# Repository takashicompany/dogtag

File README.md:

# DogTag

DogTagは9キーのコンパクトなマクロパッドです。  
100mm x 100mm 以内のPCBから組み立てます。  
リバーシブルに対応しており、2台をTRRSケーブルで接続することで分割型のマクロパッドとしても使用できます。  
その他にもロータリーエンコーダの搭載やMXソケットによるキースイッチの付け替え(ホットスワップ)も可能です。  
LEDによるアンダーグロウも可能です。  

DogTag is a compact macro pad with 9 keys.  
It is assembled from a PCB no larger than 100mm x 100mm.  
It is reversible and can be used as a split macro pad by connecting two units with a TRRS cable.  
Other features include a rotary encoder and MX sockets for hot-swapping of keyswitches.  
LED underglow is also available.  

## 必要な部品

### キットに同梱されているもの
|部品|個数|備考|
|:--|:--|:--|
|PCB|1|リードタイプと表面実装のダイオードに対応。|
|ダイオード（リードタイプ)|9||
|m2スペーサー(3.5mm)|5||
|m2ネジ(3mm)|10||
|リセットスイッチ|1||
|TRRSソケット|1||
|滑り止めシール|4||

### 別途用意するもの
|部品|個数|備考|
|:--|:--|:--|
|キースイッチ|9|Cherry MX互換のもの。|
|キーキャップ|9|全て1u。Chery MX互換のもの。|
|Pro Micro|1||
|USBケーブル|1|Pro MicroとPCを接続します。|

### オプション
|部品|個数|備考|
|:--|:--|:--|
|コンスルー|2|Pro Microに取り付けます。|
|MXソケット|9|キースイッチの付け替えが可能になります。|
|ロータリーエンコーダ|1|親指に近いキーにロータリーエンコーダを取り付けることができます。
|LED(SK6812MINI-E)|4|キーボードが光ります。|

## 組み立て方

以下の組み立て方は左手用になります。
右手側の場合は基板を裏返して組み立ててください。

### 1. トッププレートとPCBを切り離す

トッププレートとPCBが結合しているので、これを切り離します。  
(場合によっては切り離し済みのケースがあります。)  

基板を接続部の折れ線に沿って曲げると切り離せます。  

残った接続部分はペンチなどで折ると取りやすいです。  
折った場所をヤスリがけすると仕上がりがキレイになります。  

### 2. ダイオードをはんだ付けする  

ダイオードを取り付けます。  
余談ですが、ダイオードは電流の向きを制御する役割があります。  
自作キーボードでは主にキーが同時に押されたことを検知する役割があります。  
以上のことは知らなくても当キーボードは完成させられますのでご安心ください🙏  

ダイオードが基板のはんだ付け穴に入るように足を曲げます。  

ダイオードをはんだ付け穴に挿します。  
ダイオードの端の黒い線が、基板の矢印(|◁)側になるようにPCBに挿します。

はんだ付けをするために基板を反対側にします。  
この時、ダイオードの足を少し開くとPCBから抜けづらくなります。  

はんだ付けを行います。  
はんだ付けがはじめての方は[こちら](https://www.youtube.com/watch?v=iCJXT3d4140)の動画を参考に進めるとスムーズに行くかと思います。  
(難しそうなイメージがありますが、要はくっついていれば良いのです)

はんだ付けが済んだら、ニッパーで足を切ります。  

合計9箇所をはんだ付けします。  
**ダイオードの向きが写真と異なっていないかを確認してください。**

### 3. リセットスイッチの取り付け

リセットスイッチはファームウェアを書き込む際などに使用します。  

取り付け位置はキーボードの手前の「RESET」の印刷がされている箇所です。  

穴にリセットスイッチの足を挿し込みます。  

基板をひっくり返してリセットスイッチの足が穴から出ていることを確認します。   

はんだ付けを行います。  

はんだ付けを済ませたらニッパーなどではんだ付け部分を切り取り、可能な限り平らにするとキーボードが安定しやすくなります。  

### 4. TRRSソケットの取り付け

TRRSソケットは、分割キーボードとして利用する場合にキーボード同士を繋げるために使います。  
単体で使う場合は使用しませんが、気が変わって両手分欲しくなっても良いように取り付けましょう笑  

取り付け位置は、基板手前側の「TRRS」と印刷されている箇所です。

穴に沿って挿し込みます。  
いくつか穴が余ってしまうのは、右手側で利用する際の穴です。  

はんだ付けの際にひっくり返す時にTRRSソケットが抜けてしまう場合は、マスキングテープなどで固定すると良いです。  

ひっくり返して、リセットスイッチと同様にはんだ付けを行います。  

### 4.5 LEDの取り付け

(LEDを取り付けない方は、この項目はスキップして問題ありません。)

Rev2以降の基板ではSK6812MINI-Eを取り付け、DogTagを光らせることができます。

下の写真と同じく、PCBの底面に取り付けることで表側へLEDの光が届くようになります。  

### 5. トッププレートの取り付け  

トッププレートを取り付けます。  
**取り付けるPro Microによっては、トッププレートと干渉してしまう場合があるので、必要に応じてヤスリなどで削るとスムーズに取り付けられるかと思います。**  

ネジが2種類同梱されている場合は、左の頭が小さいネジはトッププレート側(表側)、右の頭が大きいネジはボトムプレート側(底面側)に使用します。  

取り付けにはネジとスペーサーを使用します。  

赤丸の位置に、スペーサーをネジで固定します。  

このように5箇所にスペーサーを取り付けます。  

最後にトッププレートを取り付けます。  
スペーサーとトッププレートをネジで固定します。  

### 6. Pro Microの取り付け。

Pro Microはキーボードの頭脳となる部分です。  
キースイッチが押されたことを検知して、PCにキーの入力を伝えます。  
Pro MicroをPCBに固定する際は[コンスル](https://shop.yushakobo.jp/products/31)ーという部品を用いるのがオススメです。  
コンスルーを使うと、Pro Microを基板から楽に取り外せるので、メンテナンスがしやすかったり、他の自作キーボードに使い回すことが容易になります。  

[コンスルーがはんだ付けされたものが遊舎工房さんで販売されている](https://shop.yushakobo.jp/products/a0500ph?variant=37665498497185)ので、難しそう…と感じた方は購入するのもアリだと思います。

Pro Microにコンスルーを挿します。  
左手側の場合はPro Microのチップなどが配置されている側が裏になるようにしてください。  
(右手側の場合は逆にチップ側が表になるようにしてください。)  

コンスルーでPro MicroとPCBを接続します。  

Pro Microをはんだ付けします。  
トッププレートとPro Microがぶつかってしまうことがあるので、正しく挿されているか側面から確認するとミスを避けられます。 

全ての端子をはんだ付けできたら完了です。  

### 7. キースイッチのはんだ付け

キースイッチを取り付けます。  

キースイッチの取り付け方は2種類あります。

#### a. キースイッチを直にはんだ付けする場合

キースイッチをトッププレートに挿し込みます。  

キースイッチの足がはんだ付け穴(周りが銀箔になっている)から出ていることを確認します。　　

キースイッチの足をはんだ付けします。  

#### b. MXソケットを使う場合  

MXソケットをPCBにはんだ付けし、キースイッチをMXソケットで固定する方式です。  
手間が増えますが、キースイッチを付け替えられることがメリットです。  

MXソケットのプリントのうち片方のはんだ付け箇所に事前にはんだを載せておきます。(予備ハンダというそうです。)  

MXソケットをピンセットで抑えながら、予備ハンダを溶かしながらMXソケットの片方をはんだ付けします。  

もう一方のはんだ付け箇所もはんだ付けして完了です。  
表面からキースイッチをMXソケットに挿し込みます。  

9箇所にキースイッチを挿し込めば完了です。  

### 8. ゴム足を付ける

ゴム足をつけて完成です。  

底面に取り付けます。  

### 9. キーキャップを取り付ける

最後にキーキャップを取り付けて完成です。  

### 10. ファームウェアの書き込み

ファームウェアは[Remap](https://remap-keys.app/catalog/1vSyBflE9L18u1AavBH4/firmware)から書き込めます。  
キーボードをPCに接続し、GoogleChromeで上述したサイトを開き「Flash」をクリックするとファームウェアの書き込みが始まります。  

Remapでのキーマップの書き換え方は[こちら](https://salicylic-acid3.hatenablog.com/entry/remap-manual)。

QMKへのプルリクエストは下記になります。
https://github.com/qmk/qmk_firmware/pull/15259

### 11. 自慢する
完成しましたら、ぜひSNSなどに写真を投稿頂ければと思います。  
Twitterのハッシュタグは`#DogTagMacroPad`を付けていただけば幸いです。  
キットを組み立てた感想や、キーボードを使った所感などをお待ちしております！  

また、毎週日曜日の１9時より実施されている[#KEEP_PD](https://twitter.com/hashtag/KEEB_PD?f=live)に投稿頂くこともオススメです。  
開催の告知は[@KEEB_PD](https://twitter.com/KEEB_PD)にて行われております。

ご不明な点などございましたら、[@takashicompany](https://twitter.com/takashicompany)にメンションやDM頂ければと思います！

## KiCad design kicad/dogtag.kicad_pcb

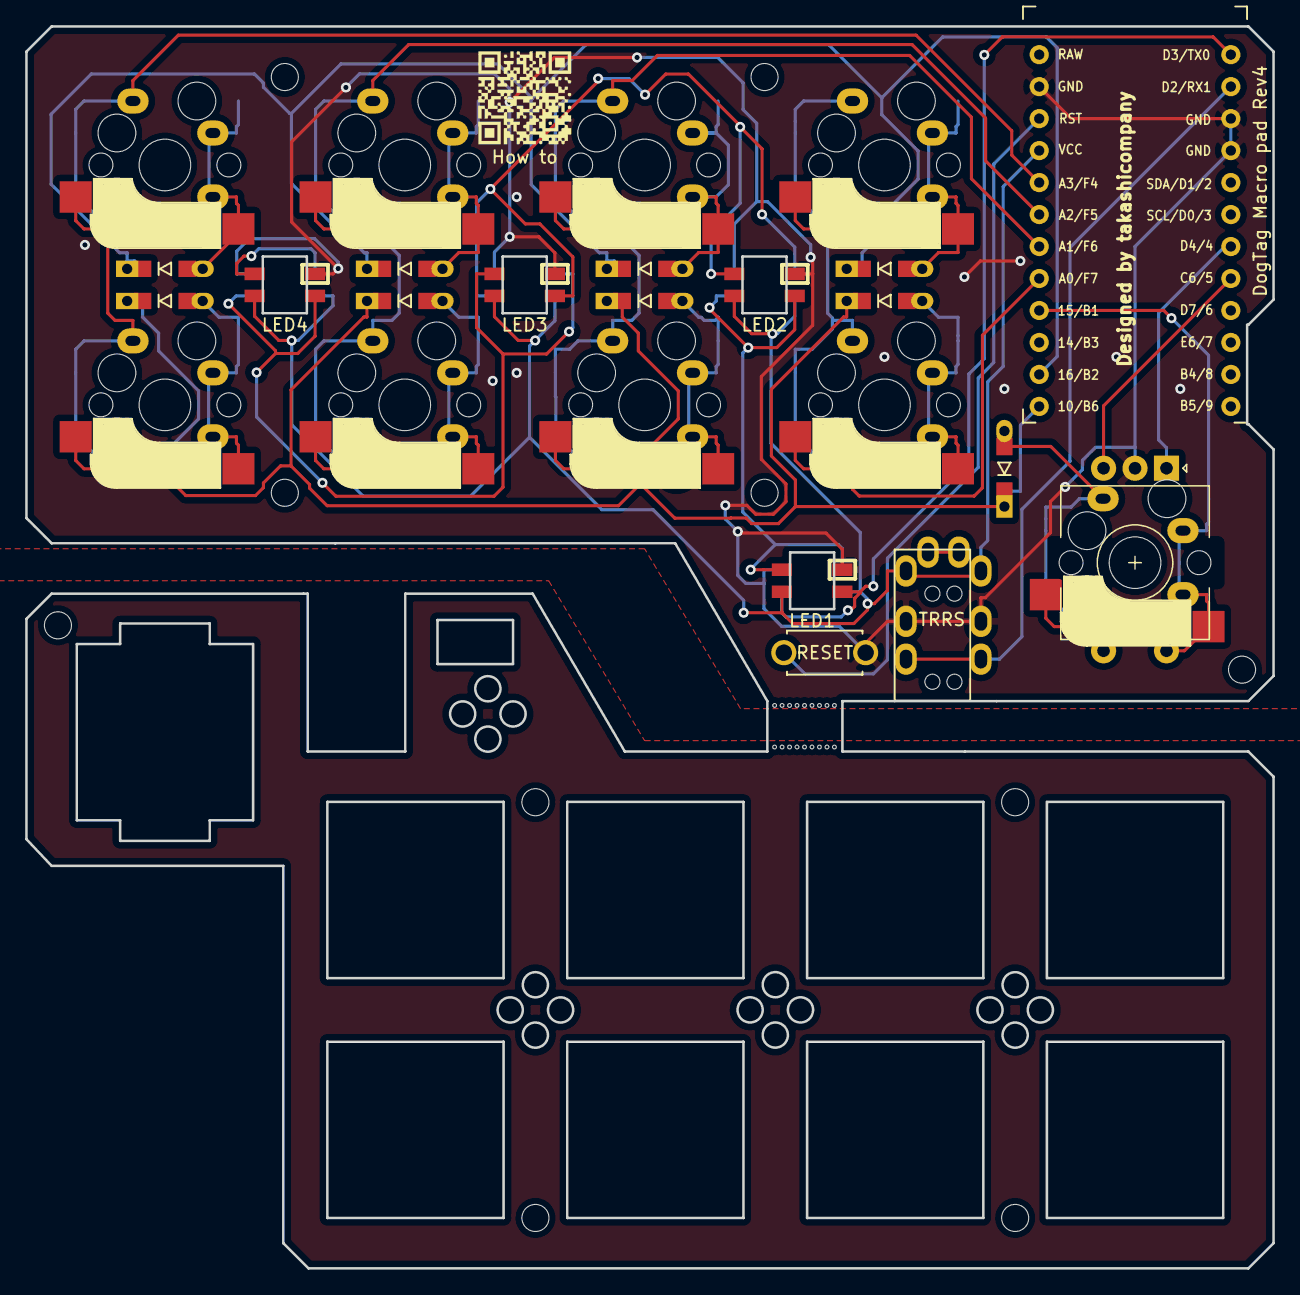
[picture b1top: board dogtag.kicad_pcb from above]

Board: 2 copper layers, 99.0 x 98.6 mm, 42 parts (0 on the bottom side), 26 nets.

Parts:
BT00, BT01: Breakaway_Tabs
D1, D2, D3, D4, D5, D6, D7, D8, D9: DIODE; D3_TH_SMD_v2_Reversible
Hole00, Hole01, Hole02, Hole03, Hole04, Hole05, Hole06, Hole07, Hole08: Val**; M2_Hole
J1: MJ-4PP-9
LED1, LED2, LED3, LED4: YS-SK6812MINI-E; SK6812MINI_bg_reversible
LH1, LH2, LH3, LH4: LED_Hole-4
RESET_SW1: SW_Push; ResetSW
RH1: ResetSW_HOLE
Ref**: Val**; M2_Hole
SW1, SW2, SW3, SW4, SW5, SW6, SW7, SW8: SW_Push; CherryMX_TH_Hotswap_Reversible_v2
SW9: RotaryEncoder_Switch; CherryMX_TH_Hotswap_Reversible_RotaryEncoder_EC11_v3
U1: ProMicro; ProMicro_v3.5_print-inside

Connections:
GND: J1.C, LED1.3, LED2.3, LED3.3, LED4.3, RESET_SW1.2, SW9.C, U1.3, U1.4, U1.23
unnamed: D1.2, SW1.2
unnamed: D2.2, SW2.2
unnamed: D3.2, SW3.2
unnamed: D4.2, SW4.2
unnamed: D5.2, SW5.2
unnamed: D6.2, SW6.2
unnamed: D7.2, SW7.2
unnamed: D8.2, SW8.2
unnamed: D9.2, SW9.S1
unnamed: LED1.2, LED2.4
unnamed: LED2.2, LED3.4
unnamed: LED3.2, LED4.4
VCC: J1.D, LED1.1, LED2.1, LED3.1, LED4.1, U1.21
col1: SW1.1, SW5.1, U1.20
col2: SW2.1, SW6.1, U1.19
col3: SW3.1, SW7.1, U1.18
col4: SW4.1, SW8.1, U1.17
col5: SW9.S2, U1.16
data: J1.B, U1.2
led: LED1.4, U1.1
reset: RESET_SW1.1, U1.22
rot-a: SW9.A, U1.7
rot-b: SW9.B, U1.8
row1: D1.1, D2.1, D3.1, D4.1, U1.14
row2: D5.1, D6.1, D7.1, D8.1, D9.1, U1.13

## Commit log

2021-11-22 画像を追加
2021-11-22 qmk用の画像
2021-11-22 サマリー
2021-11-22 順番を修正
2021-11-24 必要な部品を列挙
2021-11-24 buid guide用の画像
2021-11-24 ビルドログを追加
2021-11-24 途中までだけどコミット
2021-11-24 画像を入れた
2021-11-26 ここまで出来た
2021-11-26 改行を調整
2021-11-26 ちょっと明るくした
2021-11-26 赤丸を付けたバージョン
2021-11-26 新しい画像を追加
2022-01-31 rev1のガーバーファイルを追加
2022-03-07 youtubeリンク
2022-03-26 ハッシュタグを変更
2022-05-10 add rev4 gerber
2022-09-13 デザイン
2023-05-22 image
2023-08-02 kicad
